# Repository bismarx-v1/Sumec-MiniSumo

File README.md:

# OLDER REPO, FOR NEWEST RELEASES VISIT: [Updated repo](https://github.com/bismarx-v1/Sumec-Minisumo-main)

# MiniSumo "SUMEC" Robot Project

## Description
This GitHub repository contains the code and documentation about student-built MiniSumo robot "SUMEC". MiniSumo robots are small autonomous robots designed to compete in MiniSumo competitions, where they attempt to push their opponents out of a ring. Our other repository "Sumec-Remote" is a forked repo from p1rse, created for our own MiniSumo start remote, PCB is ours, schematic was copied from "p1rse/robot-sumo-start-module".
## Contents
- **-3D-** Provides CAD files for the mechanical components of the robot, such as the chassis and sensor mounts.
  
- **-CODE-** Contains the source code for the MiniSumo robot, including firmware for microcontrollers, sensor libraries and control diagrams.
  
- **-DOCS-** Includes robot documentation, rules for specific tournaments, and extras.

- **-PCB-** Includes PCB files, we are using KiCAD for PCB designing.

## Our suppliers
We buy our components from: 

- [Mouser Electronics](https://cz.mouser.com/?utm_id=93841169&gad_source=1)
- [GM Electronics](https://www.gme.cz)
- [TME](https://www.tme.eu/cz/en/)
- [BotLand](https://botland.cz/?gad_source=1)

## Contributing
Contributions to this project are welcome! If you have improvements, bug fixes, or new features to contribute, feel free to contact us!

## Acknowledgements
We would like to thank our school SPŠ na Proseku, our teachers, our principle, for providing resources, knowledge and top-notch equipment.

## Contact
If you have any questions, suggestions, or issues regarding this project, please feel free to contact us: 

Email - savvapopov1804@gmail.com
LinkedIn - www.linkedin.com/in/savva-popov

And follow us on the social media! 
Instagram - @sumec_minisumo_bot

**Sending love, from Czech Republic!**

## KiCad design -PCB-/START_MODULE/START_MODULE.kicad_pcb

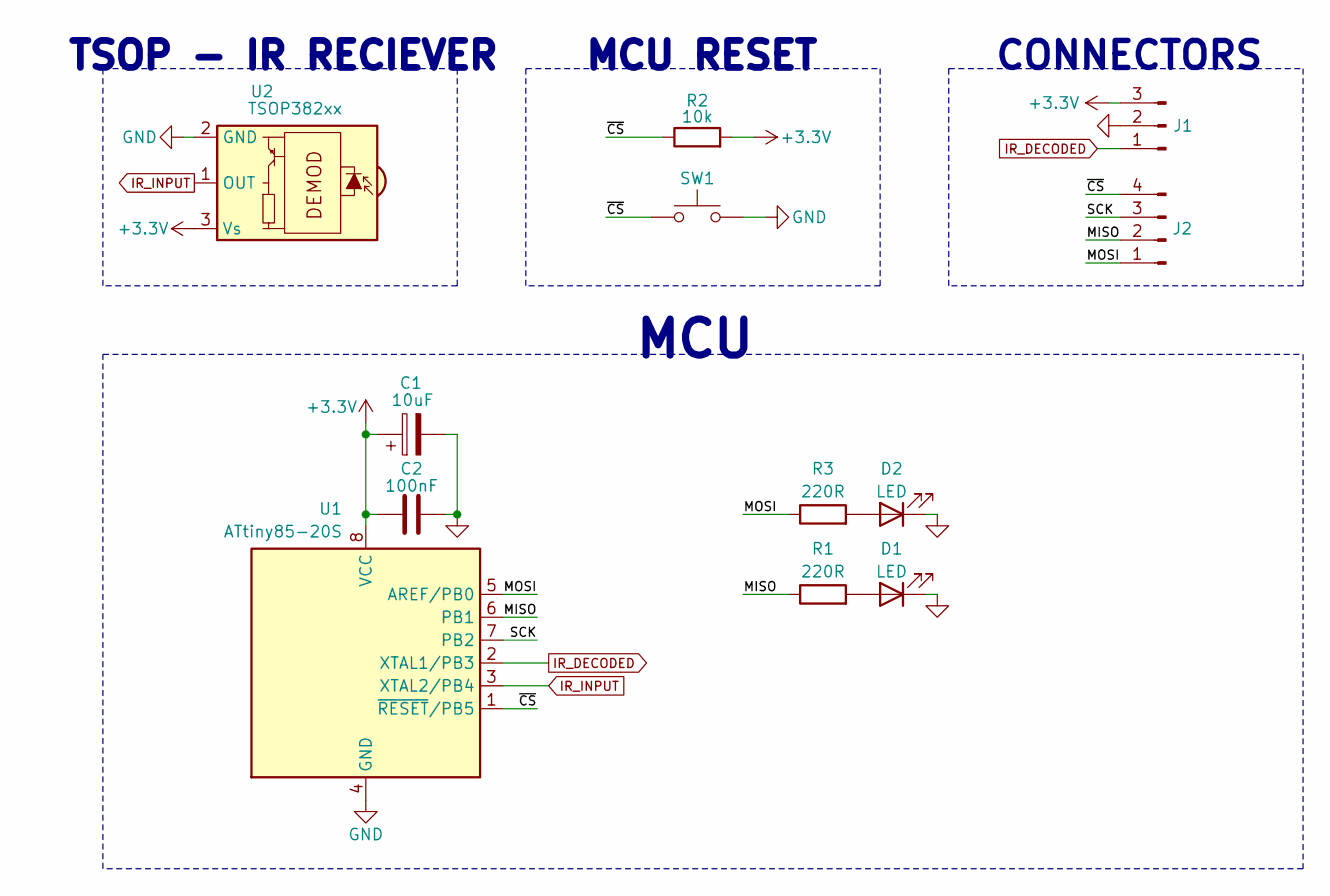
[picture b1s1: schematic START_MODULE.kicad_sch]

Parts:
C1: 10uF; CP_EIA-3216-18_Kemet-A_Pad1.58x1.35mm_HandSolder
C2: 100nF; C_0805_2012Metric_Pad1.18x1.45mm_HandSolder
D1, D2: LED; LED_0805_2012Metric_Pad1.15x1.40mm_HandSolder
J1: Conn_01x03_Pin; PinHeader_1x03_P2.54mm_Vertical
J2: Conn_01x04_Pin; PinHeader_1x04_P2.54mm_Vertical
R1, R3: 220R; R_0805_2012Metric_Pad1.20x1.40mm_HandSolder
R2: 10k; R_0805_2012Metric_Pad1.20x1.40mm_HandSolder
SW1: SW_Push; SW_SPST_EVQPE1
U1: ATtiny85-20S; SOIC-8W_5.3x5.3mm_P1.27mm
U2: TSOP382xx; Vishay_MINICAST-3Pin

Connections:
+3.3V: C1.1, C2.1, J1.3, R2.2, U1.8 (VCC), U2.3 (Vs)
/MISO: J2.2, R1.1, U1.6 (PB1)
/MOSI: J2.1, R3.1, U1.5 (AREF/PB0)
/SCK: J2.3, U1.7 (PB2)
/~CS: J2.4, R2.1, SW1.2, U1.1 (~RESET/PB5)
GND: C1.2, C2.2, D1.1 (K), D2.1 (K), J1.2, SW1.1, U1.4 (GND), U2.2 (GND)
IR_DECODED: J1.1, U1.2 (XTAL1/PB3)
IR_INPUT: U1.3 (XTAL2/PB4), U2.1 (OUT)
unnamed: D1.2 (A), R1.2
unnamed: D2.2 (A), R3.2

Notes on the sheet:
MCU
TSOP - IR RECIEVER
CONNECTORS
MCU RESET

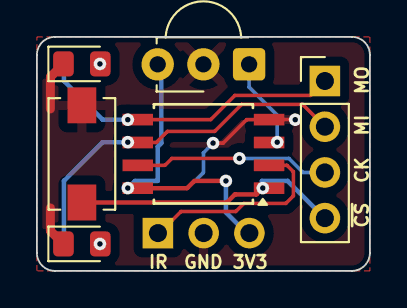
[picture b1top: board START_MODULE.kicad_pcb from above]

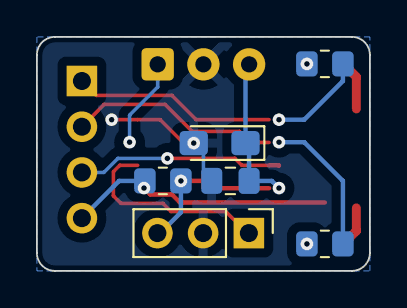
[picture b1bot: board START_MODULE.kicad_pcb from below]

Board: 2 copper layers, 18.5 x 13.0 mm, 12 parts (6 on the bottom side), 10 nets.

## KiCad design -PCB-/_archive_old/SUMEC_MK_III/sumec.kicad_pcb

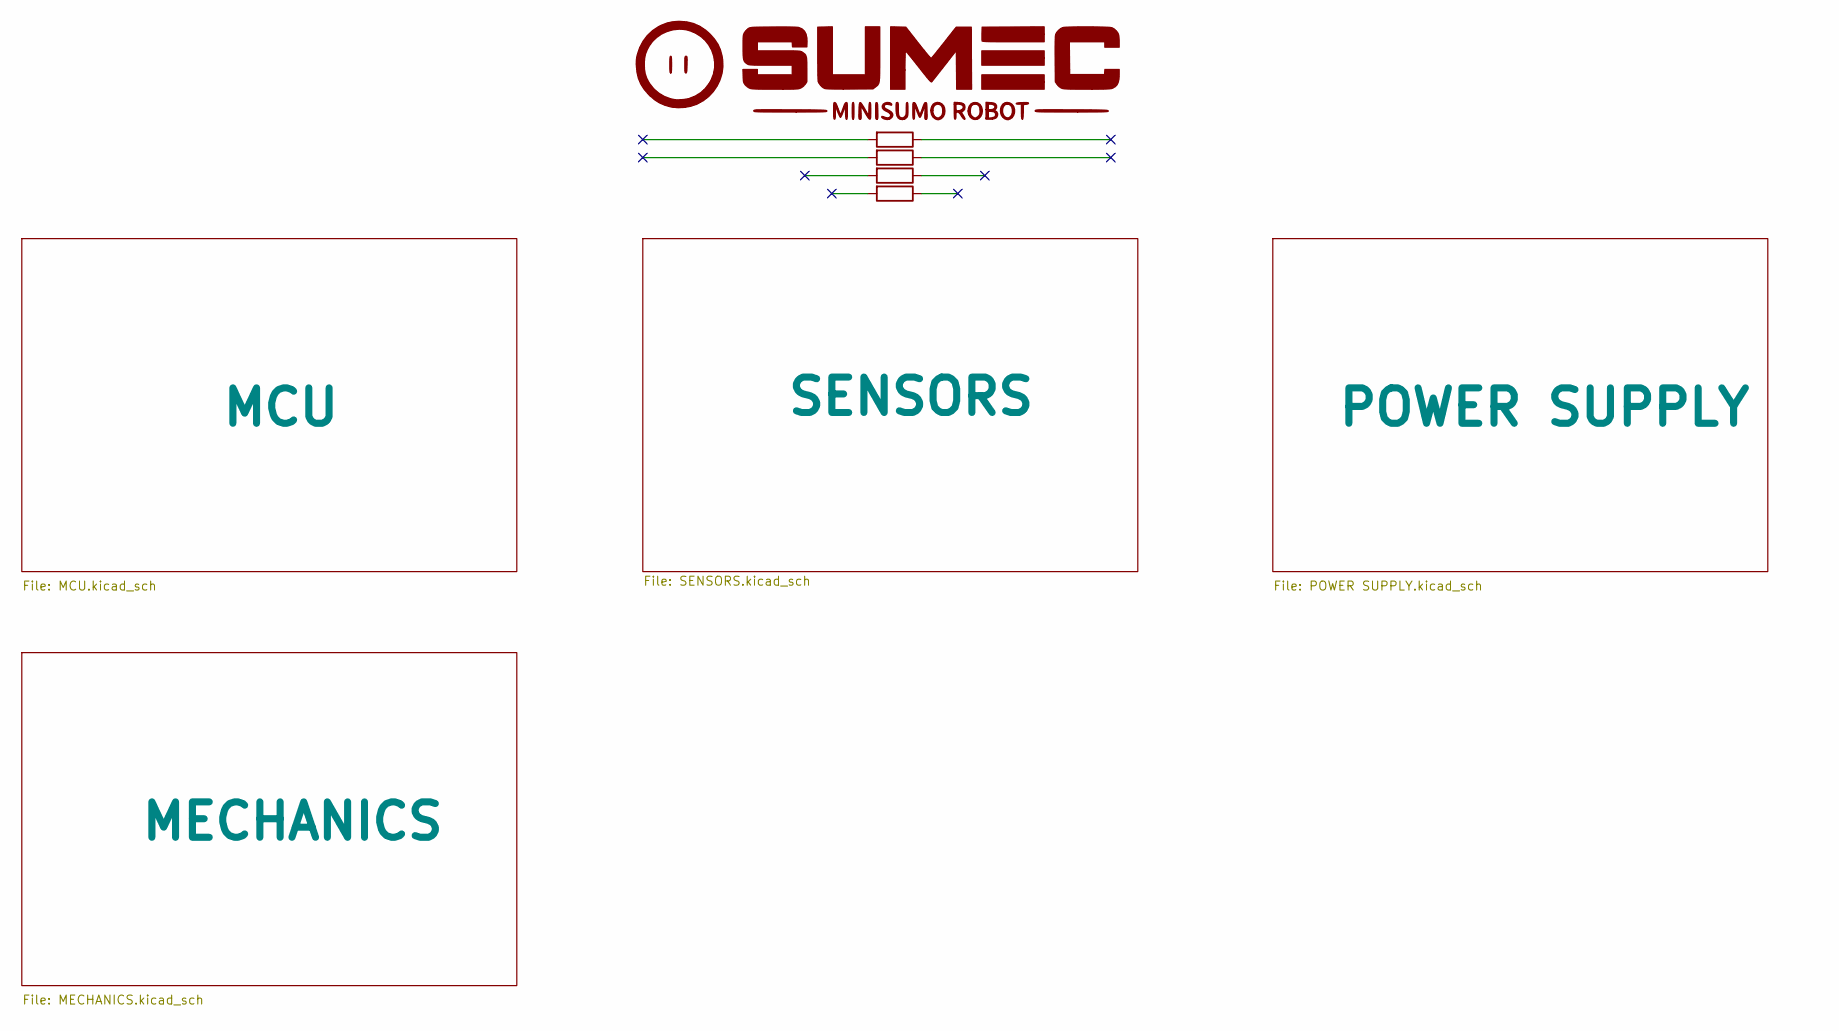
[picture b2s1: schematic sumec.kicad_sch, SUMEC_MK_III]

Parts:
R4: R; SPS LOGO
R12: R; VIGIL 2
R20: R; R2D2
R21: R; Logo

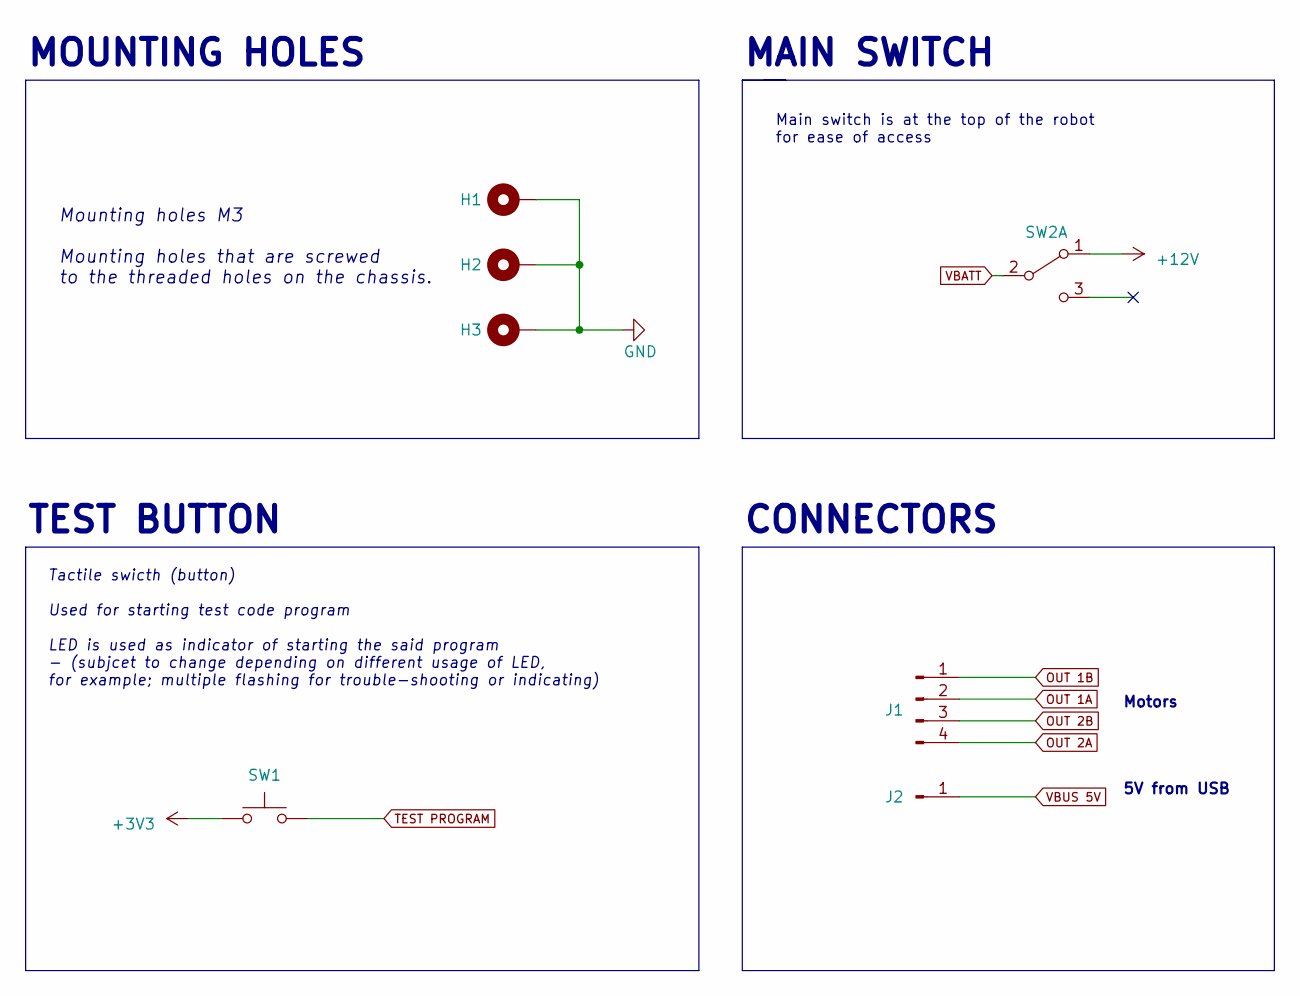
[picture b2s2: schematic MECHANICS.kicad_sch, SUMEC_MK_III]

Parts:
H1, H2, H3: MountingHole_Pad; MountingHole_3.2mm_M3_Pad
J1: Conn_01x04_Pin; JST_XH_B4B-XH-A_1x04_P2.50mm_Vertical
J2: Conn_01x01_Pin; SolderWire-0.1sqmm_1x01_D0.4mm_OD1mm
SW1: SW_Push; SW_SPST_B3U-1000P
SW2: SW_DPDT_x2; Custom_SPDT_4.8mm_Switch

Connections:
+3V3: SW1.1; also elsewhere on the board
+12V: SW2.1 (A); also elsewhere on the board
GND: H1.1, H2.1, H3.1; also elsewhere on the board
OUT 1A: J1.2; also elsewhere on the board
OUT 1B: J1.1; also elsewhere on the board
OUT 2A: J1.4; also elsewhere on the board
OUT 2B: J1.3; also elsewhere on the board
TEST PROGRAM: SW1.2; also elsewhere on the board
VBATT: SW2.2 (B); also elsewhere on the board
VBUS 5V: J2.1; also elsewhere on the board

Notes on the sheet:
MOUNTING HOLES
Mounting holes M3 Mounting holes that are screwed to the threaded holes on the chassis.
MAIN SWITCH
Motors
TEST BUTTON
Main switch is at the top of the robot for ease of access
5V from USB
CONNECTORS
Tactile swicth (button) Used for starting test code program LED is used as indicator of starting the said program - (subjcet to change depending on different usage of LED, for example; multiple flashing for trouble-shooting or indicating)

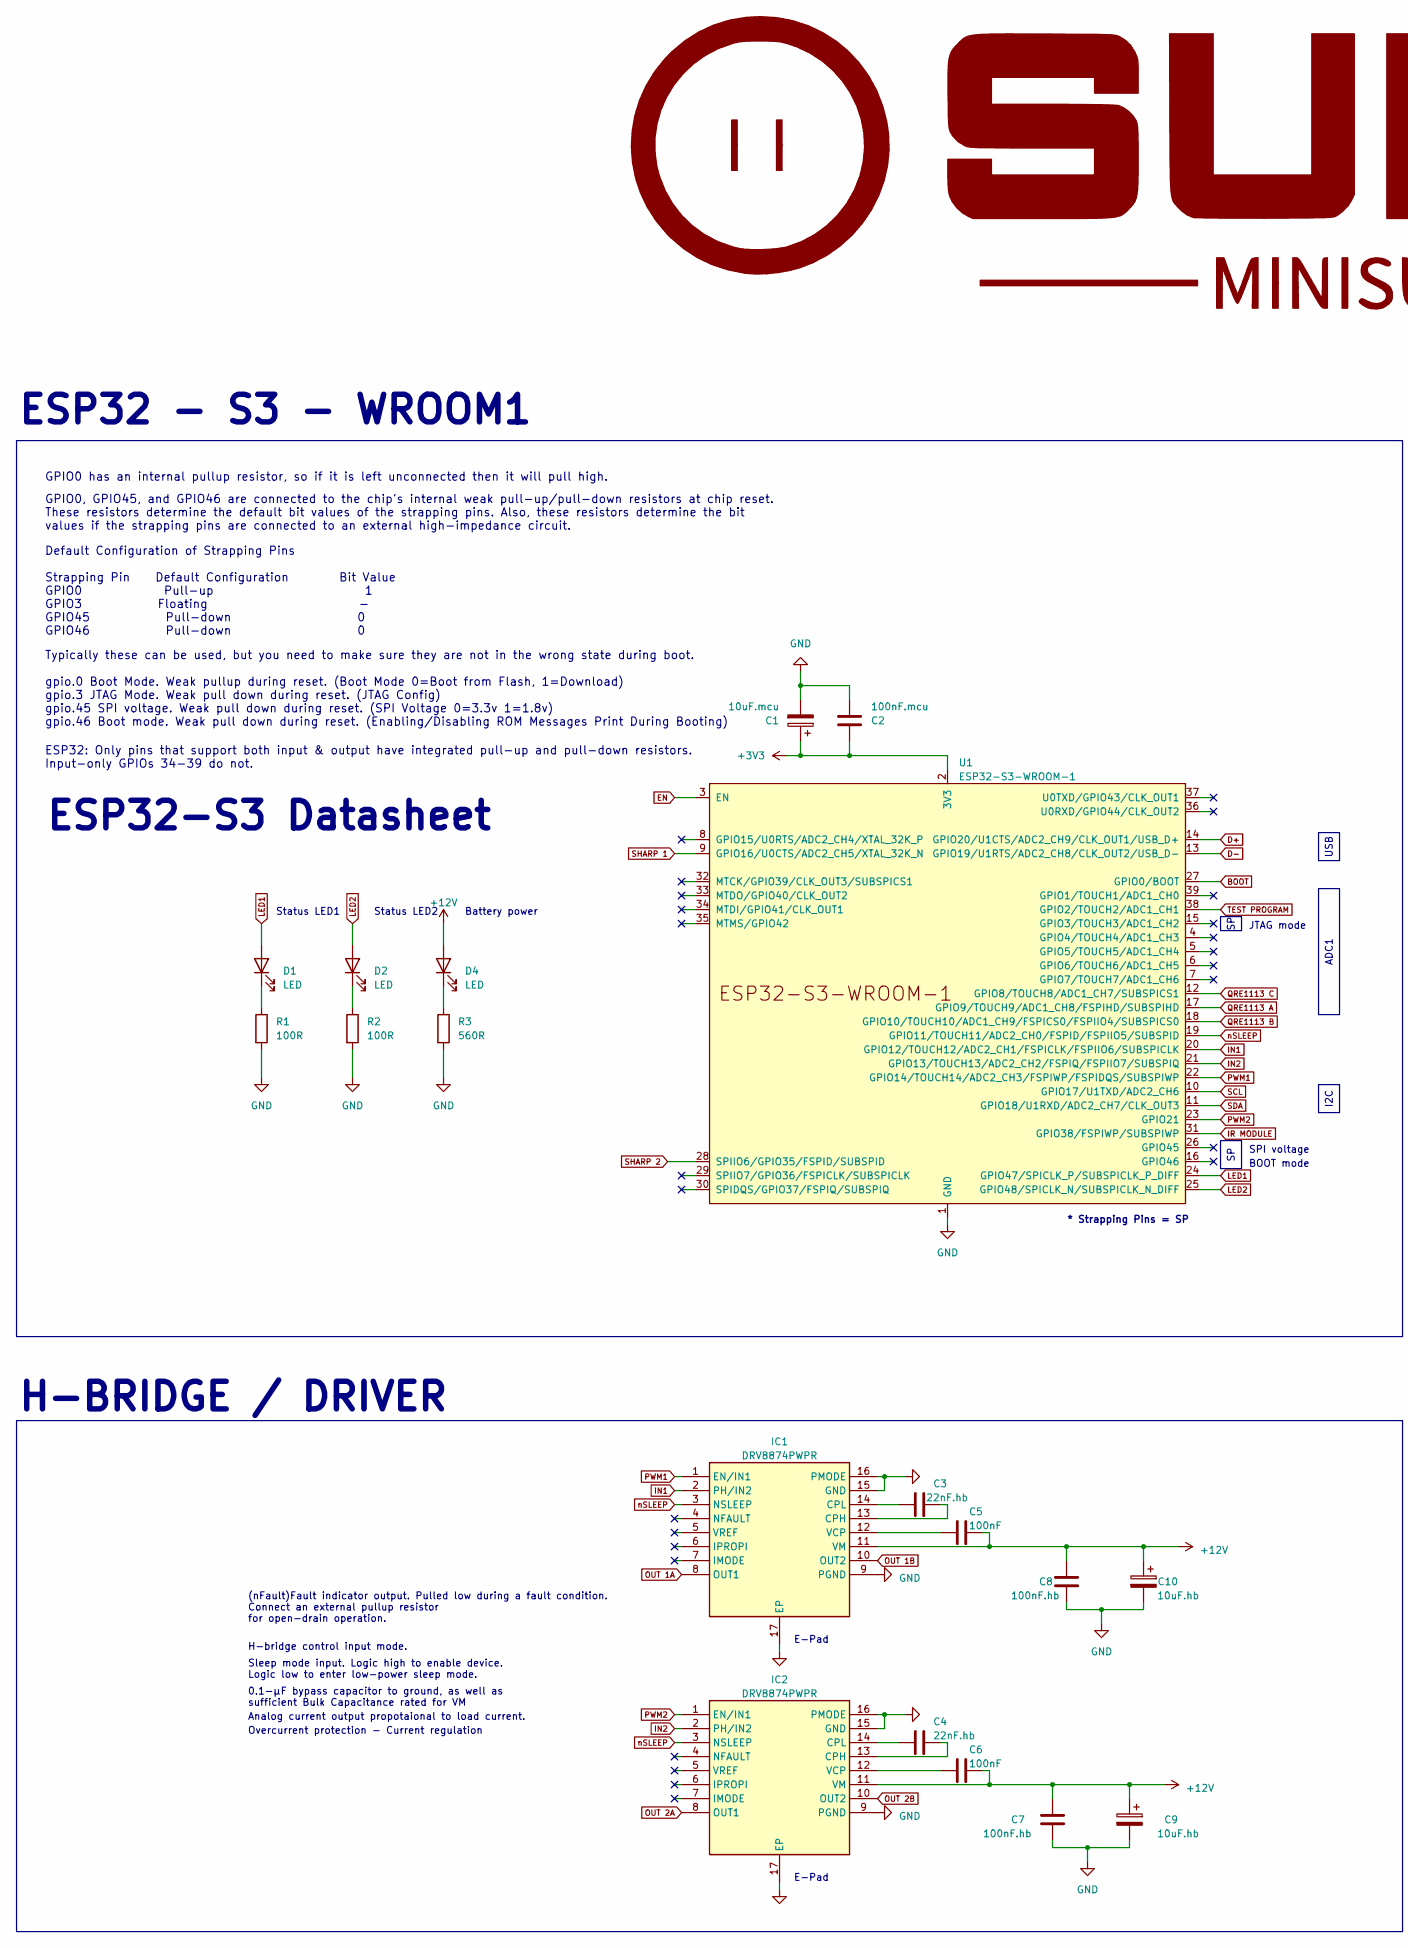
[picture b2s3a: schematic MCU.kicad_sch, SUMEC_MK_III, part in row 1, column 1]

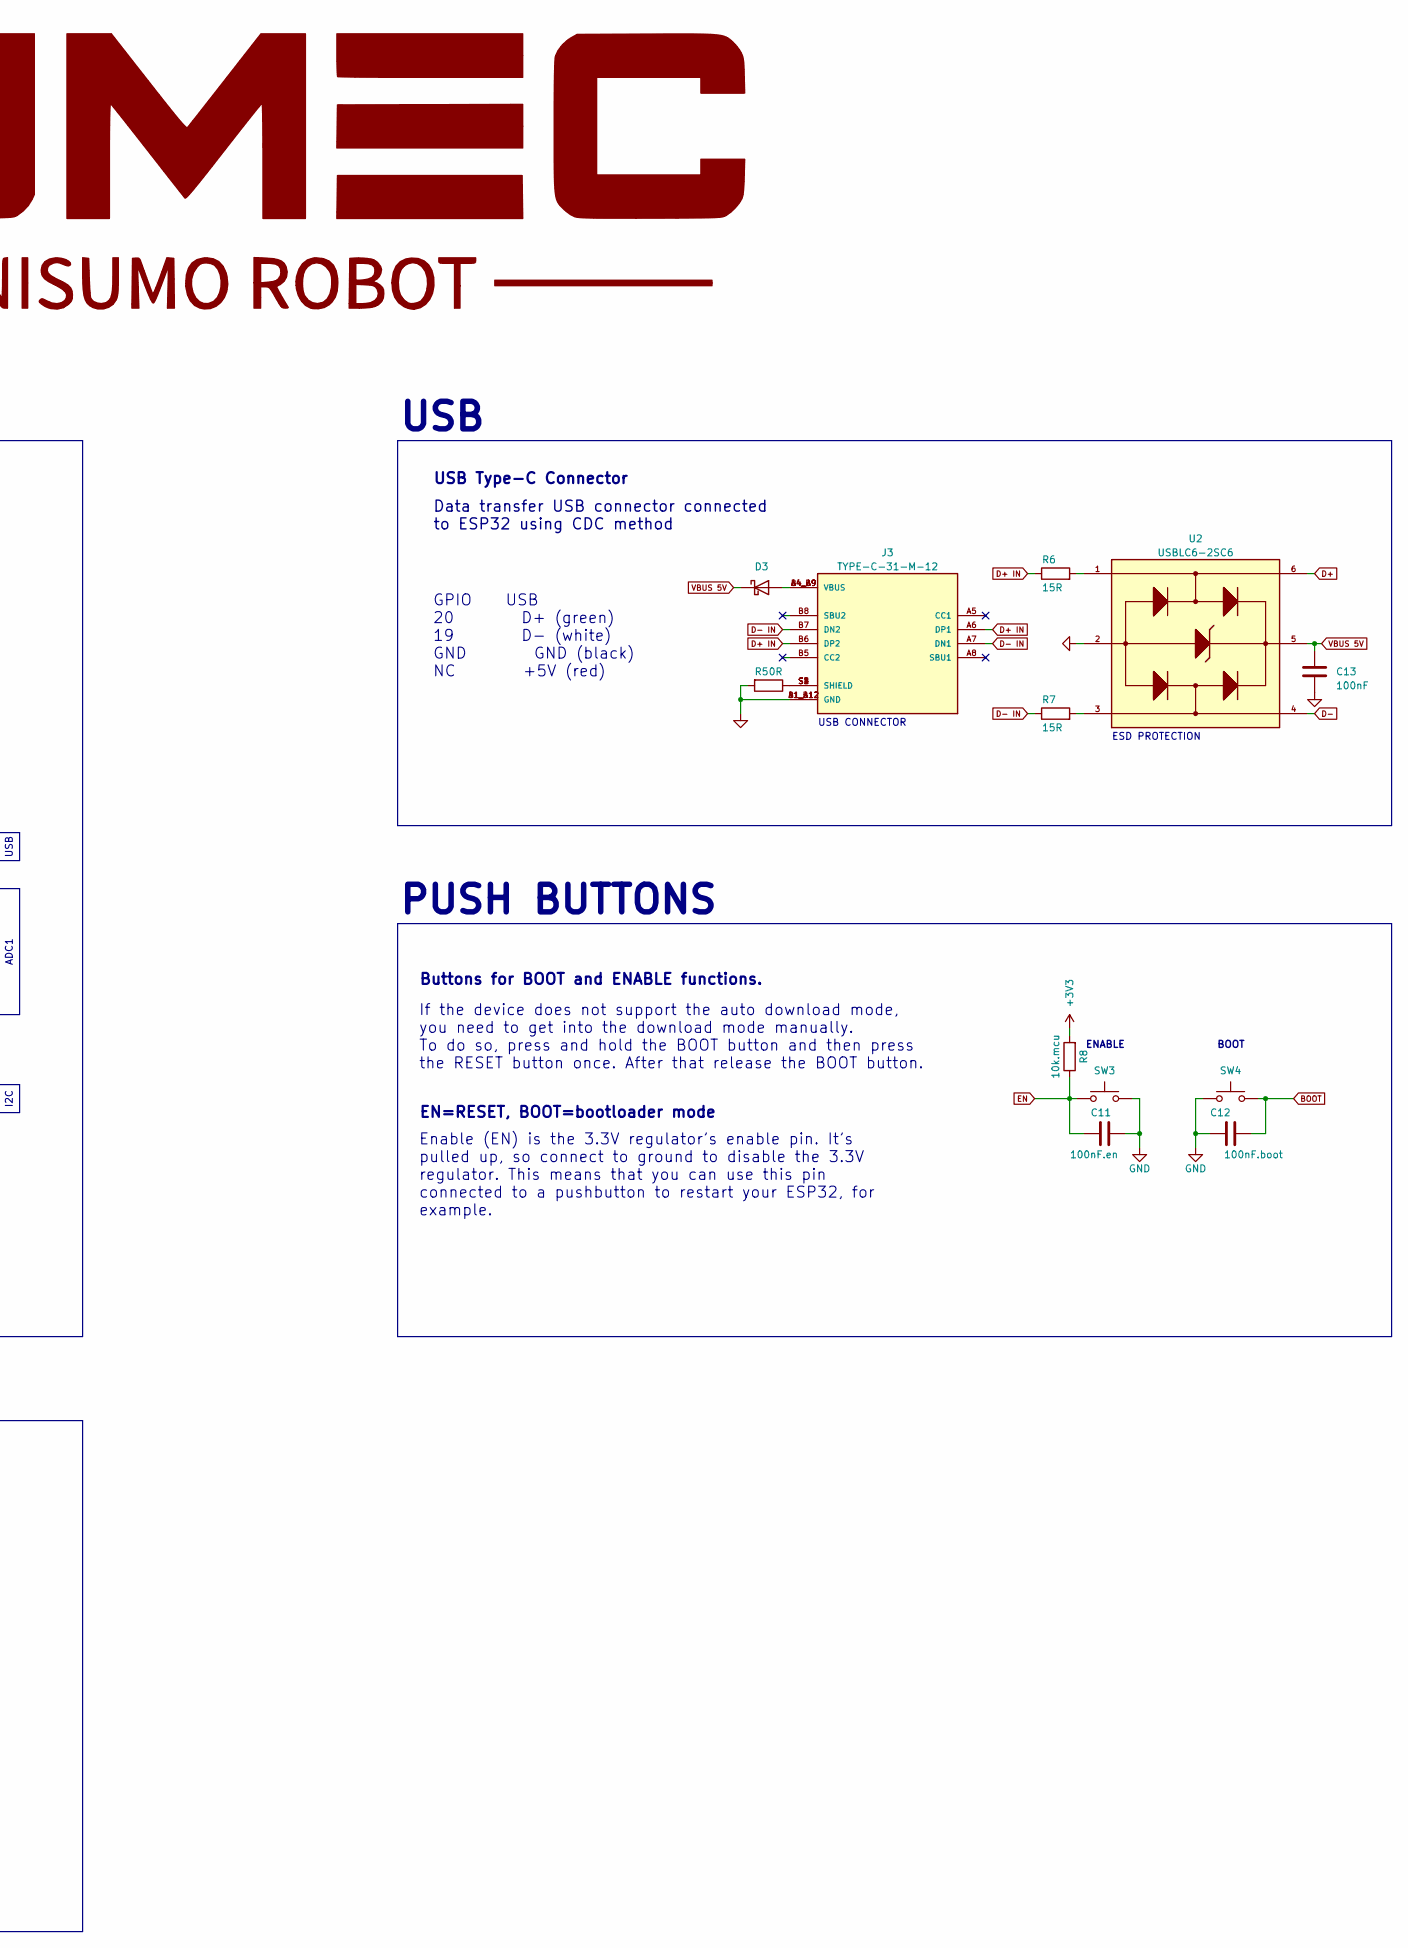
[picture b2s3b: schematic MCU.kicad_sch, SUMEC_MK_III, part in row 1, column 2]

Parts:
C1: 10uF.mcu; CP_EIA-3216-18_Kemet-A_Pad1.58x1.35mm_HandSolder
C2: 100nF.mcu; C_0805_2012Metric_Pad1.18x1.45mm_HandSolder
C3, C4: 22nF.hb; C_0805_2012Metric_Pad1.18x1.45mm_HandSolder
C5, C6, C13: 100nF; C_0805_2012Metric_Pad1.18x1.45mm_HandSolder
C7, C8: 100nF.hb; C_0805_2012Metric_Pad1.18x1.45mm_HandSolder
C9, C10: 10uF.hb; CP_EIA-3216-18_Kemet-A_Pad1.58x1.35mm_HandSolder
C11: 100nF.en; C_0805_2012Metric_Pad1.18x1.45mm_HandSolder
C12: 100nF.boot; C_0805_2012Metric_Pad1.18x1.45mm_HandSolder
D1, D2, D4: LED; LED_0805_2012Metric_Pad1.15x1.40mm_HandSolder
D3: D_Schottky; D_1206_3216Metric_Pad1.42x1.75mm_HandSolder
IC1, IC2: DRV8874PWPR; DRV8874; Manufacturer_Part_Number DRV8874PWPR; Mouser Part Number 595-DRV8874PWPR
J3: TYPE-C-31-M-12; USB_Type_C; PARTREV 2020.12.08
R1, R2: 100R; R_0805_2012Metric_Pad1.20x1.40mm_HandSolder
R3: 560R; R_0805_2012Metric_Pad1.20x1.40mm_HandSolder
R5: 0R; R_1206_3216Metric_Pad1.30x1.75mm_HandSolder
R6, R7: 15R; R_0805_2012Metric_Pad1.20x1.40mm_HandSolder
R8: 10k.mcu; R_0805_2012Metric_Pad1.20x1.40mm_HandSolder
SW3, SW4: SW_Push; SW_SPST_B3U-1000P
U1: ESP32-S3-WROOM-1
U2: USBLC6-2SC6; TSOT-23-6_HandSoldering

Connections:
+3V3: C1.1, C2.1, R8.2, U1.2 (3V3); also elsewhere on the board
+12V: C5.1, C6.1, C7.2, C8.2, C9.1, C10.1, D4.2 (A), IC1.11 (VM), IC2.11 (VM); also elsewhere on the board
BOOT: C12.1, SW4.2, U1.27 (GPIO0/BOOT)
D+: U1.14 (GPIO20/U1CTS/ADC2_CH9/CLK_OUT1/USB_D+), U2.6
D+ IN: J3.A6 (DP1), J3.B6 (DP2), R6.1
D-: U1.13 (GPIO19/U1RTS/ADC2_CH8/CLK_OUT2/USB_D-), U2.4
D- IN: J3.A7 (DN1), J3.B7 (DN2), R7.1
EN: C11.1, R8.1, SW3.2, U1.3 (EN)
GND: C1.2, C2.2, C7.1, C8.1, C9.2, C10.2, C11.2, C12.2, C13.2, IC1.9 (PGND), IC1.15 (GND), IC1.16 (PMODE), IC1.17 (EP), IC2.9 (PGND), IC2.15 (GND), IC2.16 (PMODE), IC2.17 (EP), J3.A1_B12 (GND), J3.B1_A12 (GND), R1.2, R2.2, R3.2, R5.2, SW3.1, SW4.1, U1.1 (GND), U1.40 (GND), U1.41 (GND), U2.2; also elsewhere on the board
IN1: IC1.2 (PH/IN2), U1.20 (GPIO12/TOUCH12/ADC2_CH1/FSPICLK/FSPIIO6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)
IN2: IC2.2 (PH/IN2), U1.21 (GPIO13/TOUCH13/ADC2_CH2/FSPIQ/FSPIIO7/S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)
IR MODULE: U1.31 (GPIO38/FSPIWP/SUBSPIWP); also elsewhere on the board
LED1: D1.2 (A), U1.24 (GPIO47/SPICLK_P/SUBSPICLK_P_DIFF)
LED2: D2.2 (A), U1.25 (GPIO48/SPICLK_N/SUBSPICLK_N_DIFF)
unnamed: D1.1 (K), R1.1
unnamed: D2.1 (K), R2.1
unnamed: D3.2 (A), J3.A4_B9 (VBUS), J3.B4_A9 (VBUS)
unnamed: D4.1 (K), R3.1
unnamed: C3.2, IC1.13 (CPH)
unnamed: C3.1, IC1.14 (CPL)
unnamed: C5.2, IC1.12 (VCP)
unnamed: C4.2, IC2.13 (CPH)
unnamed: C4.1, IC2.14 (CPL)
unnamed: C6.2, IC2.12 (VCP)
unnamed: J3.S1 (SHIELD), J3.S2 (SHIELD), J3.S3 (SHIELD), J3.S4 (SHIELD), R5.1
unnamed: R6.2, U2.1
unnamed: R7.2, U2.3
OUT 1A: IC1.8 (OUT1); also elsewhere on the board
OUT 1B: IC1.10 (OUT2); also elsewhere on the board
OUT 2A: IC2.8 (OUT1); also elsewhere on the board
OUT 2B: IC2.10 (OUT2); also elsewhere on the board
PWM1: IC1.1 (EN/IN1), U1.22 (GPIO14/TOUCH14/ADC2_CH3/FSPIWP/FSPIDQS/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)
PWM2: IC2.1 (EN/IN1), U1.23 (GPIO21)
QRE1113 A: U1.17 (GPIO9/TOUCH9/ADC1_CH8/FSPIHD/SUBSPIHD); also elsewhere on the board
QRE1113 B: U1.18 (GPIO10/TOUCH10/ADC1_CH9/FSPICS0/FSPIIO4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); also elsewhere on the board
QRE1113 C: U1.12 (GPIO8/TOUCH8/ADC1_CH7/SUBSPICS1); also elsewhere on the board
SCL: U1.10 (GPIO17/U1TXD/ADC2_CH6); also elsewhere on the board
SDA: U1.11 (GPIO18/U1RXD/ADC2_CH7/CLK_OUT3); also elsewhere on the board
SHARP 1: U1.9 (GPIO16/U0CTS/ADC2_CH5/XTAL_32K_N); also elsewhere on the board
SHARP 2: U1.28 (SPIIO6/GPIO35/FSPID/SUBSPID); also elsewhere on the board
TEST PROGRAM: U1.38 (GPIO2/TOUCH2/ADC1_CH1); also elsewhere on the board
VBUS 5V: C13.1, D3.1 (K), U2.5; also elsewhere on the board
nSLEEP: IC1.3 (NSLEEP), IC2.3 (NSLEEP), U1.19 (GPIO11/TOUCH11/ADC2_CH0/FSPID/FSPIIO5/S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)

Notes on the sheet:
ADC1
USB
I2C
0.1-µF bypass capacitor to ground, as well as sufficient Bulk Capacitance rated for VM
SPI voltage
Enable (EN) is the 3.3V regulator’s enable pin. It’s pulled up, so connect to ground to disable the 3.3V regulator. This means that you can use this pin connected to a pushbutton to restart your ESP32, for example.
USB CONNECTOR
Status LED2
Sleep mode input. Logic high to enable device. Logic low to enter low-power sleep mode.
USB Type-C Connector
GPIO0, GPIO45, and GPIO46 are connected to the chip's internal weak pull-up/pull-down resistors at chip reset. These resistors determine the default bit values of the strapping pins. Also, these resistors determine the bit values if the strapping pins are connected to an external high-impedance cir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
E-Pad
Overcurrent protection - Current regulation
ENABLE
Analog current output propotaional to load current.
GPIO USB 20 D+ (green) 19 D- (white) GND GND (black) NC +5V (red)
H-BRIDGE / DRIVER
Status LED1
H-bridge control input mode.
BOOT mode
If the device does not support the auto download mode, you need to get into the download mode manually. To do so, press and hold the BOOT button and then press the RESET button once. After that release the BOOT button.
* Strapping Pins = SP
Battery power
ESP32 - S3 - WROOM1
Default Configuration of Strapping Pins Strapping Pin Default Configuration Bit Value GPIO0 Pull-up 1 GPIO3 Floating - GPIO45 Pull-down 0 GPIO46 Pull-down 0
JTAG mode
PUSH BUTTONS
GPIO0 has an internal pullup resistor, so if it is left unconnected then it will pull high.
ESD PROTECTION
Buttons for BOOT and ENABLE functions.
Typically these can be used, but you need to make sure they are not in the wrong state during boot. gpio.0 Boot Mode. Weak pullup during reset. (Boot Mode 0=Boot from Flash, 1=Download) gpio.3 JTAG Mode. Weak pull down during reset. (JTAG Config) gpio.45 SPI voltage. Weak pull down during reset. (S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
ESP32: Only pins that support both input & output have integrated pull-up and pull-down resistors. Input-only GPIOs 34-39 do not.
ESP32-S3 Datasheet
EN=RESET, BOOT=bootloader mode
Data transfer USB connector connected to ESP32 using CDC method
BOOT
(nFault)Fault indicator output. Pulled low during a fault condition. Connect an external pullup resistor for open-drain operation.

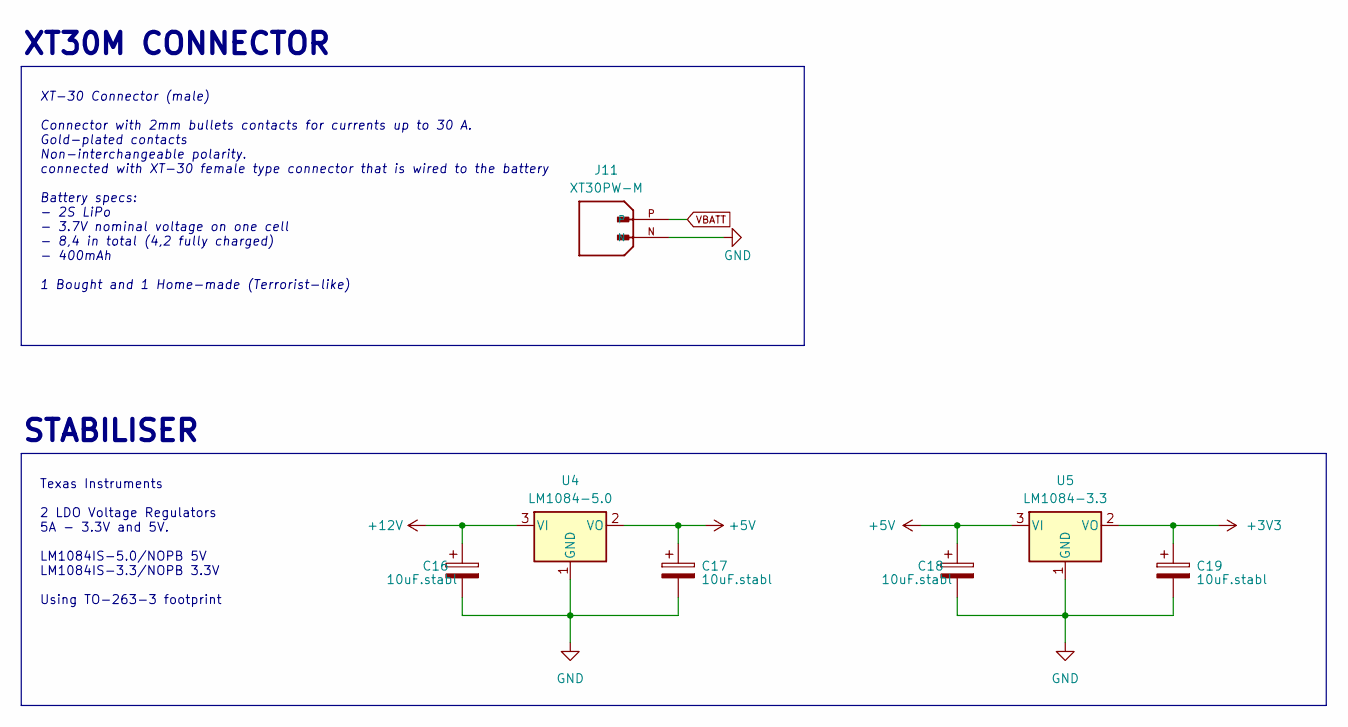
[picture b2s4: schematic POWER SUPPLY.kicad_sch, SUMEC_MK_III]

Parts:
C16, C17, C18, C19: 10uF.stabl; CP_EIA-3216-18_Kemet-A_Pad1.58x1.35mm_HandSolder
J11: XT30PW-M; AMASS_XT30PW-M; PARTREV 1.2
U4: LM1084-5.0; TO-263-3_TabPin2
U5: LM1084-3.3; TO-263-3_TabPin2

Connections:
+3V3: C19.1, U5.2 (VO); also elsewhere on the board
+5V: C17.1, C18.1, U4.2 (VO), U5.3 (VI); also elsewhere on the board
+12V: C16.1, U4.3 (VI); also elsewhere on the board
GND: C16.2, C17.2, C18.2, C19.2, J11.N, U4.1 (GND), U5.1 (GND); also elsewhere on the board
VBATT: J11.P; also elsewhere on the board

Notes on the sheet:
Texas Instruments 2 LDO Voltage Regulators 5A - 3.3V and 5V. LM1084IS-5.0/NOPB 5V LM1084IS-3.3/NOPB 3.3V Using TO-263-3 footprint
XT-30 Connector (male) Connector with 2mm bullets contacts for currents up to 30 A. Gold-plated contacts Non-interchangeable polarity. connected with XT-30 female type connector that is wired to the battery Battery specs: - 2S LiPo - 3.7V nominal voltage on one cell - 8,4 in total (4,2 fully charge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
STABILISER
XT30M CONNECTOR

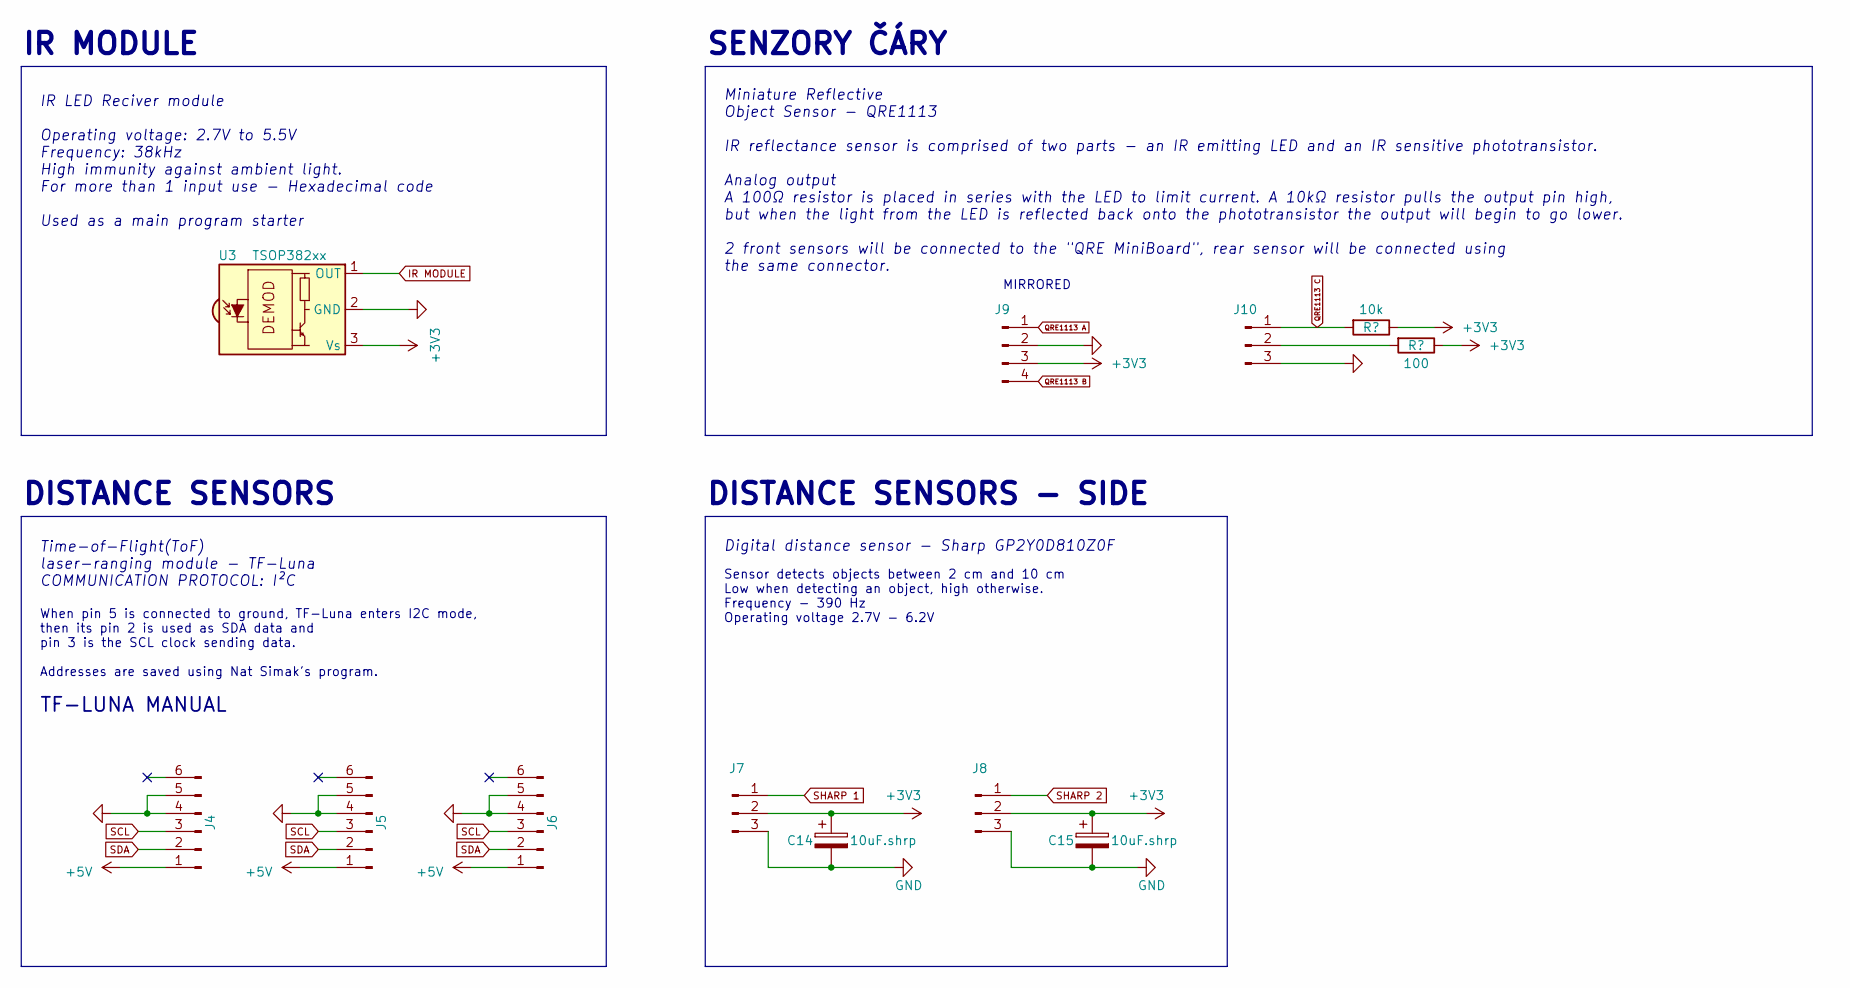
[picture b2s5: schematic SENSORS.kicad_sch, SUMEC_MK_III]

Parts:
C14, C15: 10uF.shrp; CP_EIA-3216-18_Kemet-A_Pad1.58x1.35mm_HandSolder
J4, J5, J6: Conn_01x06_Pin; Molex_PicoBlade_53398-0671_1x06-1MP_P1.25mm_Vertical
J7, J8, J10: Conn_01x03_Pin; Molex_PicoBlade_53398-0371_1x03-1MP_P1.25mm_Vertical
J9: Conn_01x04_Pin; Molex_PicoBlade_53398-0471_1x04-1MP_P1.25mm_Vertical
R9: 10k; R_0805_2012Metric_Pad1.20x1.40mm_HandSolder
R10: 100; R_0805_2012Metric_Pad1.20x1.40mm_HandSolder
U3: TSOP382xx; TSOP

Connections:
+3V3: C14.1, C15.1, J7.2, J8.2, J9.3, R9.1, R10.1, U3.3 (Vs); also elsewhere on the board
+5V: J4.1, J5.1, J6.1; also elsewhere on the board
GND: C14.2, C15.2, J4.4, J4.5, J5.4, J5.5, J6.4, J6.5, J7.3, J8.3, J9.2, J10.3, U3.2 (GND); also elsewhere on the board
IR MODULE: U3.1 (OUT); also elsewhere on the board
unnamed: J10.2, R10.2
QRE1113 A: J9.1; also elsewhere on the board
QRE1113 B: J9.4; also elsewhere on the board
QRE1113 C: J10.1, R9.2; also elsewhere on the board
SCL: J4.3, J5.3, J6.3; also elsewhere on the board
SDA: J4.2, J5.2, J6.2; also elsewhere on the board
SHARP 1: J7.1; also elsewhere on the board
SHARP 2: J8.1; also elsewhere on the board

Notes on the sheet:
Time-of-Flight(ToF) laser-ranging module - TF-Luna COMMUNICATION PROTOCOL: I²C
IR LED Reciver module Operating voltage: 2.7V to 5.5V Frequency: 38kHz High immunity against ambient light. For more than 1 input use - Hexadecimal code Used as a main program starter
Digital distance sensor - Sharp GP2Y0D810Z0F
IR MODULE
SENZORY ČÁRY
When pin 5 is connected to ground, TF-Luna enters I2C mode, then its pin 2 is used as SDA data and pin 3 is the SCL clock sending data. Addresses are saved using Nat Simak's program.
Sensor detects objects between 2 cm and 10 cm Low when detecting an object, high otherwise. Frequency - 390 Hz Operating voltage 2.7V - 6.2V
Miniature Reflective Object Sensor - QRE1113 IR reflectance sensor is comprised of two parts - an IR emitting LED and an IR sensitive phototransistor. Analog output A 100Ω resistor is placed in series with the LED to limit current. A 10kΩ resistor pulls the output pin high, but when the light from 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
TF-LUNA MANUAL
DISTANCE SENSORS
MIRRORED
DISTANCE SENSORS - SIDE

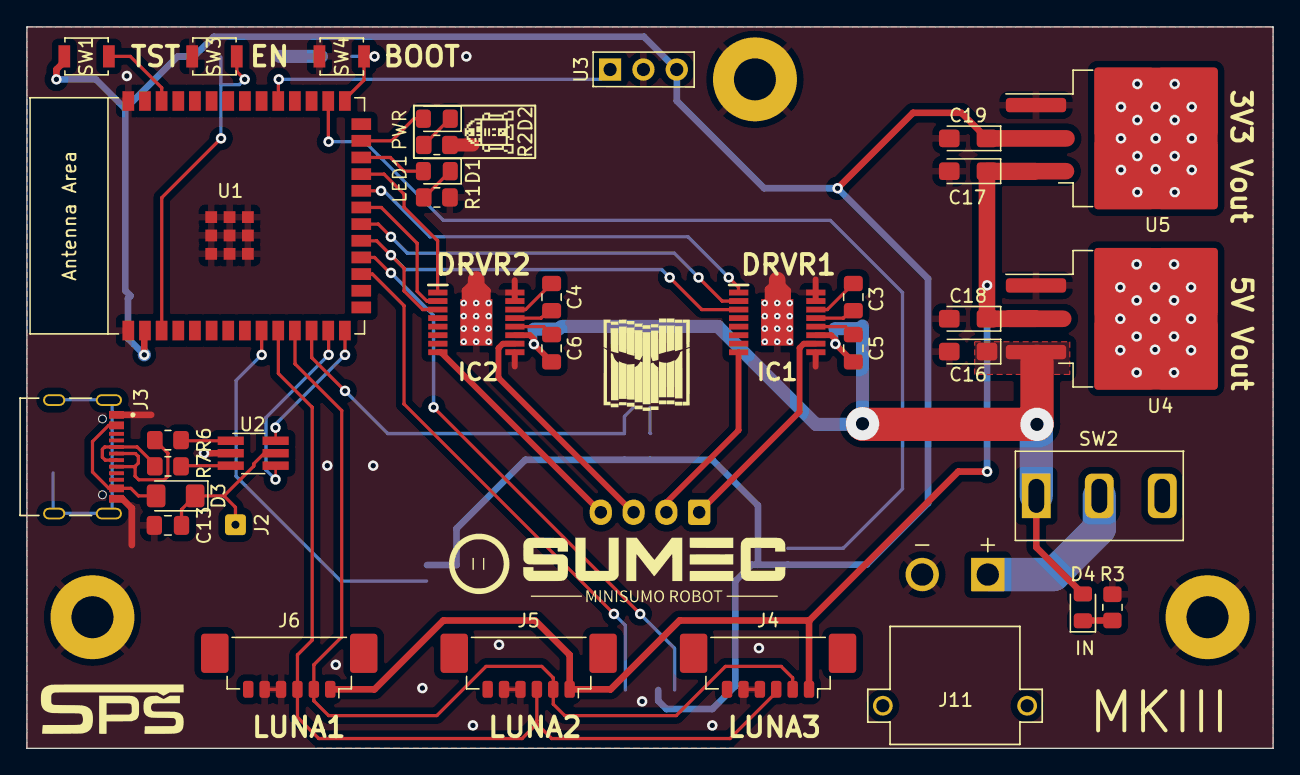
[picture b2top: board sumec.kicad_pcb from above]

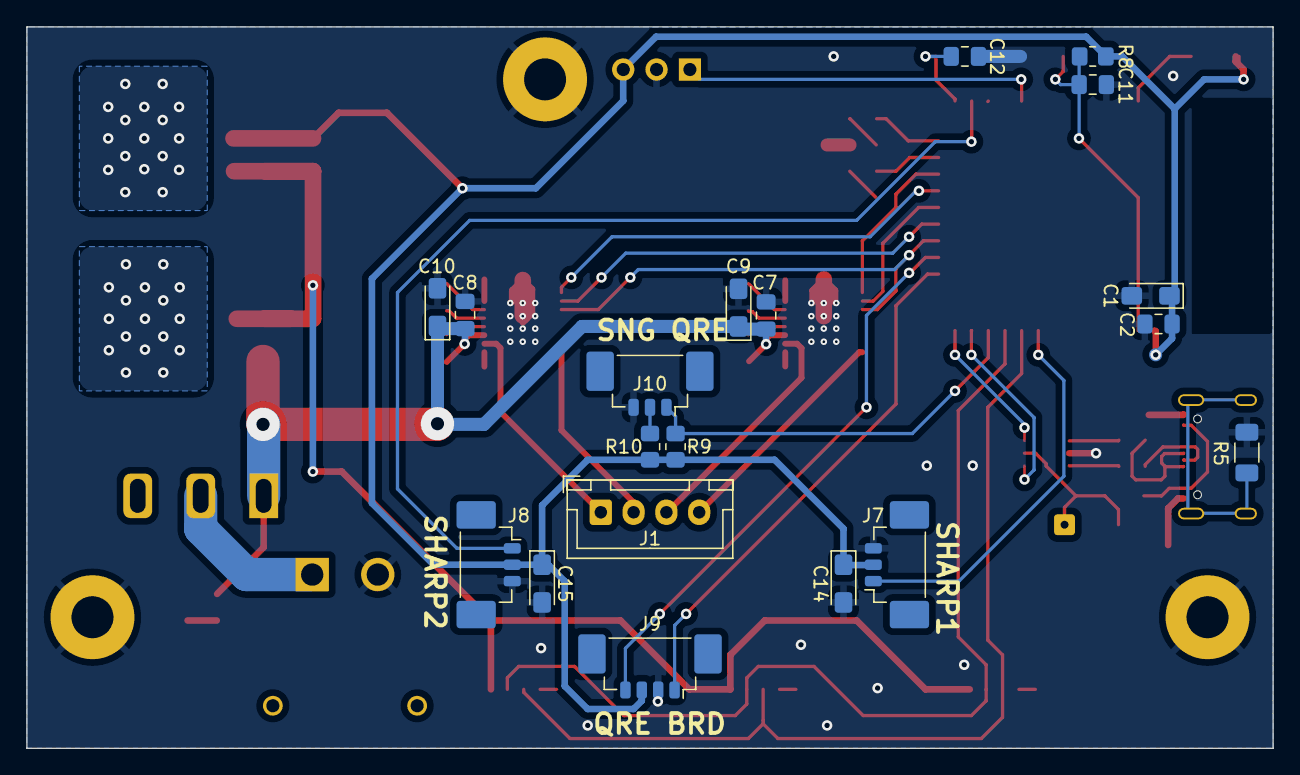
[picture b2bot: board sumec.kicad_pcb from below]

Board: 2 copper layers, 95.0 x 55.0 mm, 61 parts (19 on the bottom side), 46 nets.
